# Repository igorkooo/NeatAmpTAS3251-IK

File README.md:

# NeatAmpTAS3251 — 2×170W Class D Amplifier with I2S Input & DSP

> ⚠️ **Hobby project** — no deadlines, no warranties, no guarantees. Use at your own risk.

2×170 W Class-D amplifier based on the Texas Instruments TAS3251, featuring an ESP32-S3 controller, DSP-ready architecture, USB-C programming, and a low-noise multi-rail power supply.

---

## Overview

This project builds on the excellent [NeatAmpTAS3251](https://github.com/jmf13/NeatAmpTAS3251/tree/master)
design by jmf13 and extends it with:

- **ESP32-S3** — WiFi control, I2C management of TAS3251 (volume, EQ, fault monitoring)
- **Output inductors** — dual footprint for Coilcraft XGL1712-103MED and Würth 7443631000
  for comparative distortion testing
- **ADAU1466 DSP ready** — I2S input connector, power supply, and I2C interface prepared
  for future DSP integration
- **Revised power supply** — fully redesigned for lower noise and better thermal performance
- **EasyEDA Pro** — migrated from KiCad v9 for simplified JLCPCB prototyping workflow

The complete V1.2 hardware schematic is available in [Schematic.pdf](Schematic.pdf).

<p align="center"><em>V1.2 PCB, top view</em></p>

---

## Release Notes

### Version 1.2 (schematic + PCB layout done, DRC clean, not yet produced)
- **Important fix — ESP32-S3 module pins 28/29/30 (IO35/IO36/IO37) no longer
  used.** On the ESP32-S3-WROOM-1U-N8R8 these pins are wired internally to the
  Octal PSRAM and must stay unconnected. V1.0/V1.1 used them for SW2 + C51
  (IO35) and for the SK9822 status LED data/clock (IO36/IO37 via R18/R17).
  Using them corrupts PSRAM and crashes the firmware. Changes (netlist
  [Netlist_Class_D_amp_2026-10-30.enet](Netlist_Class_D_amp_2026-10-30.enet)):
  - Module pins 28, 29, 30 → **no connection**.
  - Status LED U8 SDI → R18 (27 Ω) → **IO8** (module pin 12).
  - Status LED U8 CKI → R17 (27 Ω) → **IO9** (module pin 17).
  - SW2 + C51 (100 nF debounce) + TP12 → **IO10** (module pin 18), with a
    new **R51 10 kΩ** pull-up to 3.3V.
  - IO8, IO9 and IO10 are **no longer on H2**. H2 pins 7, 8 and 10 are now
    not connected.
- Firmware already follows this mapping: LEDs on IO8/IO9, PSRAM in Octal mode
  (see [ESP32-S3 module pinout](#esp32-s3-module-pinout) and the
  [firmware README](tas/README.md#reserved-pins-do-not-use)).
- PCB re-routed for the new connections. DRC passes. Board outline,
  connector positions and the heatsink area are unchanged from V1.0/V1.1.
- Silkscreen revision text updated to **V 1.2**.
- [Schematic.pdf](Schematic.pdf), the 3D render and the new top-view render
  ([Pictures/PCB_3D_TOP.png](Pictures/PCB_3D_TOP.png)) are re-exported from
  V1.2.
- V1.0/V1.1 boards can be reworked to the same firmware mapping. See the
  [V1.0/V1.1 rework checklist](tas/README.md#hardware-v10v11-rework-checklist-before-first-power-up),
  including the list of differences that remain after rework.

### Version 1.1
- **Important fix** — ESP32 USB-C connector was rotated 180° in V1.0, making the
  connector unusable when assembled. Now fixed.
- Added complete JLCPCB production specifications (see
  [Production Details](#production-details-jlcpcb)) as used for the first
  prototype batch.

### Version 1.0
- PCB routing completed for the first prototype revision.
- EasyEDA Pro project migrated to the new `.eprj2` project format.
- Development performed using **EasyEDA Pro V3.2.149** (V1.2 changes made
  with **V3.2.209**).
- Latest layout improvements include routing optimisation, power distribution refinement, grounding improvements, and thermal optimisation.

---

## Status

**Version:** 1.0/1.1 (Prototype), 1.2 (layout done, not yet produced)

⚠️ **V1.0/V1.1 boards need rework before the first power-up**: remove C51,
R17 and R18, and bodge the LEDs to IO8/IO9. V1.0 also needs UART flashing
because of the rotated USB-C connector. Follow the
[V1.0/V1.1 rework checklist](tas/README.md#hardware-v10v11-rework-checklist-before-first-power-up).

⚠️ This is the first public prototype release. The hardware has **not yet been validated in real-world operation**. It should be considered experimental until prototype testing is completed.

---

## Power Supply Architecture

The power supply is a multi-rail design optimised for low noise on sensitive analog paths
while keeping thermal dissipation manageable across all operating conditions.

### Rail Overview

| Rail | Voltage | Chip | Purpose |
|------|---------|------|---------|
| PVDD | 36V | External PSU | TAS3251 output stage (H-bridges) |
| 13.2V | Buck | LMQ66410 | Intermediate rail for GVDD chain |
| 12V GVDD | LDO | TPS7A4701 | TAS3251 gate drive (GVDD_A, GVDD_B, VDD) |
| 5V | Buck | LMQ66430 | System 5V bus, USB-C OR node |
| 3.3V digital | Buck | AP63203 | ESP32-S3, STM32, ADAU1466, TAS DAC_DVDD |
| 3.3V analog | LDO | TPS7A2033 | TAS3251 DAC_AVDD only |

### 12V GVDD Chain — LMQ66410 → TPS7A4701

The gate drive supply uses a two-stage approach: a switching regulator handles the large
36V→13.2V step efficiently, followed by a low-noise LDO for the final 13.2V→12V drop. ESP32 senses GOOD_13.2V on IO39 and once stable, it triggers 12V analog power via IO38.

```
PVDD (36V) → LMQ66410 (buck, 1.25MHz) → 13.2V → TPS7A4701 (LDO) → 12V GVDD
```

- **LMQ66410**: 36V input, 1.25MHz switching frequency (RT = 39.2kΩ), feedback
  R_FBT = 49.9kΩ / R_FBB = 4.12kΩ
- **TPS7A4701**: 1A LDO, 4µVrms noise, 82dB PSRR @ 100Hz, output set via ANY-OUT
  pin programming to 12.0V (pins 0P2V + 0P8V + 3P2V + 6P4V1 → GND)
- A ferrite bead (BLM31PG121SN1L) is placed between the 13.2V rail and TPS7A4701
  input for additional HF noise isolation

> **Why two stages?** A direct linear regulator from 36V to 12V at even 50mA load
> would dissipate ~1.2W in a small SMD package. The buck + LDO combination keeps
> total dissipation under 0.8W while achieving better noise performance than a
> single-stage buck alone.

### 5V Rail — LMQ66430

```
PVDD (36V) → LMQ66430 (buck, 1.25MHz) → 5V
```

- Feedback: R_FBT = 49.9kΩ / R_FBB = 24.9kΩ
- Feeds the 5V OR node (see USB-C section)
- Sources the 3.3V digital buck and 3.3V analog LDO

### 3.3V Digital Rail — AP63203

```
5V OR rail → AP63203 (fixed 3.3V buck) → 3.3V digital
```

- Fixed 3.3V output — no external feedback resistors
- Powers: ESP32-S3, STM32F030, ADAU1466 digital, TAS3251 DAC_DVDD
- Starts automatically on power-up (EN tied to VIN)
- Output: 2× 10µF ceramic + 1× 47µF electrolytic

### 3.3V Analog Rail — TPS7A2033

```
5V OR rail → TPS7A2033 (LDO) → 3.3VA
```

- Ultra-low noise LDO: 7µVrms, 95dB PSRR
- Feeds **only** TAS3251 DAC_AVDD — kept isolated from noisy digital loads
- Enabled by default via 100kΩ pull-up to 3.3V digital; ESP32-S3 can disable via
  ENABLE_3.3V GPIO IO40 for controlled power sequencing
- Input/output decoupling: 1µF Samsung CL10B105KB8NQNC (C5199872) on both pins

### USB-C Power OR

The board supports powering the digital section from either the main 36V supply
or a USB-C connection, enabling ESP32-S3 programming without the main supply present.

```
PVDD (36V) → LMQ66430 → 5V → Schottky D1 ─┐
                                             ├─ 5V OR rail → AP63203 → 3.3V digital
USB-C VBUS (5V) ────────→ 1N5819 D2 ────────┘
```

- When 36V is present: LMQ66430 supplies the 5V OR rail; USB-C Schottky is
  reverse-biased
- When USB-C only (programming mode): USB VBUS supplies 3.3V digital via AP63203;
  TAS3251 analog section remains unpowered
- 1MΩ discharge resistor on VBUS for clean hot-plug behaviour

---

## Microcontroller — ESP32-S3 controlling TAS3251

The ESP32-S3-WROOM-1U-N8R8 (8 MB flash, 8 MB Octal PSRAM) acts as the system controller, handling WiFi connectivity,
TAS3251 configuration, real-time monitoring, and user interface.

For the ESP32-S3 firmware workspace, including the Python environment, ESP-IDF
6.0.2 setup, build commands, and editor configuration, see the
[ESP32-S3 firmware README](tas/README.md) before continuing with the hardware
interface details below.

### Interface to TAS3251

All TAS3251 runtime control is via I2C (400kHz Fast Mode). The I2C bus is shared
with the ADAU1466 when fitted.

| Signal | ESP32-S3 GPIO | TAS3251 Pin | Notes |
|--------|--------------|-------------|-------|
| SDA | GPIO IO0 | SDA (54) | 6.8kΩ pull-up (R21) to 3.3V |
| SCL | GPIO IO45 | SCL (53) | 6.8kΩ pull-up (R22) to 3.3V |
| RESET_AMP | GPIO out IO42 | /RESET_AMP (27) | Active low; 10kΩ pull-up to 3.3V (default: not in reset) |
| DAC_MUTE | GPIO out IO1 | DAC_MUTE (45) | Active low; 10kΩ pull-down to GND (default: muted at boot) |
| /FAULT | GPIO in + IRQ IO41 | /FAULT (28) | Open-drain; 10kΩ pull-up; falling-edge interrupt |
| /CLIP_OTW | GPIO in + IRQ IO2 | /CLIP_OTW (29) | Open-drain; 10kΩ pull-up; falling-edge interrupt |

### TAS3251 I2C Address

Set by ADR pin (46):
- ADR → GND: address **0x90**
- ADR → 3.3V: address **0x92**

This pin is connected to ESP32 IO12.

### Switching Frequency Select — U13

The TAS3251 PWM switching frequency is set by a resistor from FREQ_ADJ (pin 18)
to AGND, broken out on jumper header **U13** (2x4, 2.54mm). Bridge exactly one
pin pair with a shunt; the current default is **pins 3-4 (10kΩ)**, giving the
highest switching frequency.

| U13 pins | R to AGND | Switching frequency |
|----------|-----------|----------------------|
| 3-4 | 10kΩ only | 768kHz ← highest (default) |
| 5-6 | 20kΩ only | 576kHz |
| 7-8 | 30kΩ only | 384kHz |
| 1-2 | Pulled to 3.3V | Target/slave mode (external sync via OSC_IOP/IOM) |

### What ESP32-S3 Controls via I2C

| Function | Register | Notes |
|----------|----------|-------|
| Power on/off | B0-P0-R2 | Startup/shutdown sequence |
| Volume (per channel) | B0-P0-R61/R62 | 0.5dB steps, −103dB to +24dB |
| Soft mute | B0-P0-R3 | Or via DAC_MUTE pin |
| EQ / crossover biquads | Book 0x8C pages | 15× BiQuad per channel; crossover HPF/LPF |
| Safeload (atomic update) | B0x8C-P5-R7C | Write 5 coefficients then set flag = 0x01 |
| Fault status read | B0-P0-R94/R95 | OC, UV, OTE, clock error — read after /FAULT IRQ |
| Volume ramp speed | B0-P0-R64 | Controls startup/shutdown ramp to prevent pops |

### Fault Handling

Both /FAULT and /CLIP_OTW are open-drain active-low outputs wired to ESP32-S3
interrupt-capable GPIOs. Implemented in `tas::SystemController` — see the
[ESP32-S3 firmware README](tas/README.md#status-led-u8u9) for the full
state/color breakdown:

1. /FAULT asserts → falling-edge ISR fires → read B0-P0-R94/R95 for fault
   detail, re-assert DAC_MUTE, and drop both channels to a conservative low
   volume — **implemented**
2. If OTE (over-temperature): wait for thermal recovery, then toggle
   RESET_AMP to clear the latched fault before resuming — **not yet
   implemented** (tracked as a `TODO` in `SystemController::handleFault()`;
   the amp currently just stays muted at low volume until manually reset)
3. /CLIP_OTW is non-latching — current firmware logs each occurrence only
   (no mute, no volume change); revisit if sustained clipping in practice
   turns out to warrant automatic volume reduction
4. Report fault status to Home Assistant via WiFi MQTT — **not yet
   implemented** (no WiFi/MQTT in the firmware yet)

### Visual Indicators

| LED | Colour | Condition |
|-----|--------|-----------|
| D_FAULT | Red | /FAULT asserted (hardware, no firmware needed) |
| D_CLIP | Yellow/Orange | /CLIP_OTW asserted (hardware, no firmware needed) |
| D_STATUS | 2× SK9822 (U8, U9), chained | ESP32-S3 controlled over a bit-banged 2-wire link (IO8 data / IO9 clock from V1.2 and reworked V1.0/V1.1; was IO36/IO37 on V1.0/V1.1 — not WS2812B) — see [Status LED (U8/U9)](tas/README.md#status-led-u8u9) in the firmware README for the color scheme |

Fault and clip LEDs are driven directly from the open-drain output through a 560Ω
resistor — they light up regardless of firmware state.

### ESP32-S3 Module Pinout

This table covers every pin of U6 (ESP32-S3-WROOM-1U-N8R8). The V1.0/V1.1
column comes from `Netlist_Class_D_amp_2026-07-23.enet`. The V1.2 column
comes from `Netlist_Class_D_amp_2026-10-30.enet`. **Bold** marks a change.

| Module pin | IO | V1.0/V1.1 connection | V1.2 | Firmware use (`tas_pins.h`) | Notes |
|-----------:|----|----------------------|-----------------|------------------------------|-------|
| 1, 40, 41 | GND | GND | GND | — | |
| 2 | 3V3 | 3.3V | 3.3V | — | |
| 3 | EN | SW1 (reset), C48, TP9 | unchanged | — | Reset button |
| 4–7 | IO4–IO7 | U7 pins 3–6 (XH 6-pin, + GND/3.3V) | unchanged | — | Spare / expansion |
| 8–11 | IO15–IO18 | H1 pins 1–4 | unchanged | — | Spare / expansion |
| 12 | IO8 | H2 pin 7 | **R18 → U8 SDI** (H2 pin 7 NC) | `TAS_PIN_STATUS_LED_SDI` | V1.0/V1.1: bodge from H2 pin 7 |
| 13 | IO19 | R16 → USB D− | unchanged | — | Native USB, reserved |
| 14 | IO20 | R15 → USB D+ | unchanged | — | Native USB, reserved |
| 15 | IO3 | H2 pin 4 | unchanged | — | Strapping pin, avoid |
| 16 | IO46 | H2 pin 6 | unchanged | — | Strapping pin, avoid |
| 17 | IO9 | H2 pin 8 | **R17 → U8 CKI** (H2 pin 8 NC) | `TAS_PIN_STATUS_LED_CKI` | V1.0/V1.1: bodge from H2 pin 8 |
| 18 | IO10 | H2 pin 10 | **SW2 + C51, R51 10 kΩ pull-up, TP12** (H2 pin 10 NC) | — (button not used yet) | User button, active low |
| 19 | IO11 | H2 pin 12 | unchanged | — | Spare (I2S test patch MCLK) |
| 20 | IO12 | H2 pin 14 (`ESP_TAS_ADR`) | unchanged | `TAS_PIN_AMP_ADDRESS` | Jumper H2 13-14 |
| 21 | IO13 | H2 pin 16 | unchanged | — | Spare (I2S test patch BCLK) |
| 22 | IO14 | H2 pin 18 | unchanged | — | Spare (I2S test patch LRCK) |
| 23 | IO21 | H2 pin 20 | unchanged | — | Spare (I2S test patch SDIN) |
| 24 | IO47 | U10 pin 3 (`DSP_RESET`) | unchanged | `TAS_PIN_DSP_RESET` | |
| 25 | IO48 | U10 pin 6 (`DSP_SELFBOOT`) | unchanged | `TAS_PIN_DSP_SELFBOOT` | |
| 26 | IO45 | SCL (TAS3251, R20 → U10) | unchanged | `TAS_PIN_I2C_SCL` | Strapping pin; 6.8 kΩ pull-up |
| 27 | IO0 | SDA (TAS3251, R19 → U10) | unchanged | `TAS_PIN_I2C_SDA` | Strapping pin (boot); 6.8 kΩ pull-up |
| **28** | **IO35** | ⚠️ SW2 + C51 to GND, TP12 | **not connected** | — | **Octal PSRAM, reserved** |
| **29** | **IO36** | ⚠️ R18 → `L_SDI` | **not connected** | — | **Octal PSRAM, reserved** |
| **30** | **IO37** | ⚠️ R17 → `L_CKI` | **not connected** | — | **Octal PSRAM, reserved** |
| 31 | IO38 | U15 pin 7 (`ENABLE_12V`) | unchanged | `TAS_PIN_ENABLE_12V` | Jumper U15 7-8 |
| 32 | IO39 | U15 pin 5 (`GOOD_13.2V`) | unchanged | `TAS_PIN_GOOD_13V2` | Jumper U15 5-6 |
| 33 | IO40 | U15 pin 3 (`ENABLE_3.3V`) | unchanged | `TAS_PIN_ENABLE_3V3_ANALOG` | Jumper U15 3-4 |
| 34 | IO41 | U14 pin 7 (`/FAULT`) | unchanged | `TAS_PIN_AMP_FAULT` | Jumper U14 7-8 |
| 35 | IO42 | U14 pin 5 (`RESET_AMP`) | unchanged | `TAS_PIN_AMP_RESET` | Jumper U14 5-6 |
| 36 | RXD0 (IO44) | H2 pin 5, TP11 | unchanged | — | UART0 console / flashing |
| 37 | TXD0 (IO43) | H2 pin 3, TP10 | unchanged | — | UART0 console / flashing |
| 38 | IO2 | U14 pin 3 (`/CLIP_OTW`) | unchanged | `TAS_PIN_AMP_CLIP_OTW` | Jumper U14 3-4 |
| 39 | IO1 | U14 pin 1 (`DAC_MUTE`) | unchanged | `TAS_PIN_DAC_MUTE` | Jumper U14 1-2 |

### ESP32-S3 Software Configuration

These settings must match the N8R8 module. They are seeded from
[`tas/sdkconfig.defaults`](tas/sdkconfig.defaults). See the
[firmware README](tas/README.md#key-sw-configuration-sdkconfigdefaults) for
details and for how to update an existing `sdkconfig`.

| Setting | Value | Reason |
|---------|-------|--------|
| Flash size | 8 MB (`CONFIG_ESPTOOLPY_FLASHSIZE_8MB`) | N8 = 8 MB Quad flash |
| PSRAM | enabled, **Octal** (`CONFIG_SPIRAM_MODE_OCT`), 80 MHz | R8 = 8 MB Octal PSRAM. Quad mode fails init. Octal mode is why IO35–IO37 are reserved |
| Pin map | [`tas/main/tas_pins.h`](tas/main/tas_pins.h) | Single source of truth. The build fails if a pin is set to IO35–IO37 |

### Startup Sequence

```
Power applied
  → AP63203 starts → 3.3V digital available
  → ESP32-S3 boots (~150ms)
  → ESP32 initialises I2C
  → ESP32 asserts ENABLE_12V → TPS7A4701 enables → 12V GVDD available
  → TAS3251 comes out of reset (RESET_AMP released)
  → ESP32 writes TAS3251 configuration via I2C (volume, EQ, crossover)
  → ESP32 drives DAC_MUTE high → audio path unmuted
  → System ready
```

---

## I2S Audio Input

The board accepts I2S audio from either:

- **LHY Audio DIR9001 module** (SPDIF → I2S, 24-bit 96kHz) via 6-pin 2.54mm connector
- **ADAU1466 DSP board** (future) via the same I2S connector
- **ESP32-S3 directly** (for testing/streaming) via the same GPIO pins

I2S connector pinout (2.54mm, 6-pin vertical):

| Pin | Signal |
|-----|--------|
| 1 | DATA (SDIN) |
| 2 | BCLK |
| 3 | LRCK |
| 4 | MCLK |
| 5 | +5V |
| 6 | GND |

27Ω series resistors are placed on all four signal lines between the connector and
TAS3251/ESP32-S3 for signal integrity and EMI reduction.

---

## Known Issues from Original Design

> As noted by the original author:
> - Silkscreen polarity for **C25, C26, C27, C28** was inverted — caps replaced with
>   non-polarised X7R ceramics in this revision, resolving the issue entirely.
> - Heatsink footprint required rework — addressed in PCB revision.

---

## Production Details (JLCPCB)

The first prototype batch (5 boards, V1.0/V1.1) was manufactured and assembled by
JLCPCB with the settings below. These are provided as a validated reference for
anyone reproducing the board.

### PCB Fabrication

| Parameter | Value |
|-----------|-------|
| Layers | 4 |
| Base Material | FR-4, TG155 |
| Dimensions | 155.45 × 134.33 mm |
| PCB Thickness | 1.6 mm |
| PCB Color / Silkscreen | Blue / White |
| Outer Copper Weight | 2 oz |
| Inner Copper Weight | 1 oz |
| Surface Finish | ENIG, Gold Thickness 1U" |
| Via Covering | Plugged |
| Min Via Hole/Diameter | 0.3 mm / (0.4/0.45 mm) |
| Electrical Test | Flying Probe Fully Test |
| Mark on PCB | Remove Mark |
| Appearance Quality | IPC Class 2 Standard |
| Board Outline Tolerance | ±0.2 mm (Regular) |
| Delivery Format | Single PCB |
| Silkscreen Technology | Ink-jet Printing |
| Build Time | 3 days (PCB only) |
| Weight (5 pcs) | 0.89 kg |

> **Why these choices:** TG155 handles output-stage heat better than standard
> TG135. ENIG provides flat pads which significantly improves assembly yield on
> the fine-pitch QFN packages (TAS3251 VQFN-56, LMQ66430 VQFN-14, TPS7A4701
> VQFN-20). Plugged vias are required for the via-in-pad thermal grid under the
> TAS3251 exposed pad. 2 oz outer copper carries the high-current speaker output
> and PVDD paths.

### SMT Assembly

| Parameter | Value |
|-----------|-------|
| PCBA Type | Standard |
| Assembly Side | Top Side |
| PCBA Qty | 5 |
| Edge Rails/Fiducials | Added by JLCPCB |
| Confirm Parts Placement | Yes |
| Bake Components | Yes |
| Photo Confirmation | Yes |
| Board Cleaning | Yes |
| Depanel & remove edge rails before delivery | Yes |
| Solder Paste | High temp. |
| Nitrogen Reflow Soldering | No |
| Flying Probe Test (post-assembly) | No |
| Function Test | No |
| Conformal Coating | No |
| Packaging | Antistatic bubble film |
| Panel Format | 1 × 1 |
| Build Time | 5–6 days (+4 days) |
| Product Classification | Audio Amplifiers — HS Code 851890 |
| Weight (5 assembled boards) | 2.29 kg |

> **Recommended for first runs:** *Confirm Parts Placement* and *Photo
> Confirmation* let you verify component orientation before reflow — worth it on
> any board with polarised or directional parts. *Board Cleaning* removes flux
> residue that could otherwise cause leakage currents on the high-impedance
> analog nodes (DAC_AVDD, AGND area).

### Not Assembled by JLCPCB (manual population)

The following components are excluded from the SMT order
(`Add into BOM = No` in EasyEDA) and must be hand-soldered:

- **L7–L14** — output filter inductors (Coilcraft XGL1712-103MED and
  Würth/Codaca MA5172-AE dual footprints) — order from Mouser
- **TP1–TP30** — test points (optional)

---

## Enclosure

⚠️ The supplied enclosure / 3D shell has **not passed the JLCPCB manufacturing review** and is **not recommended for fabrication** in its current state. It is included for reference only and requires redesign before production.

---

## Original Project

- Original design: [jmf13/NeatAmpTAS3251](https://github.com/jmf13/NeatAmpTAS3251/tree/master)
- License: [CC BY-SA 4.0](https://creativecommons.org/licenses/by-sa/4.0/) —
  this project inherits the same license.

---

## EasyEDA Pro Setup

**Recommended EasyEDA Pro version:** **V3.2.209** (V1.0/V1.1 were made with V3.2.149).

This repository includes a custom component library. To use it, create a symbolic
link inside your EasyEDA Pro libraries directory.

### macOS / Linux

```bash
# Navigate to your EasyEDA Pro libraries directory
cd ~/Documents/EasyEDA-Pro/libraries

# Create symlink to files from there so that app recognizes it
ln -s /path/to/git/NeatAmpTAS3251/EasyEDA-Pro/libraries/* .
```

### Windows

```cmd
:: Run Command Prompt as Administrator
cd %USERPROFILE%\EasyEDA-Pro\libraries

:: Create directory symlink
mklink /D NeatAmpTAS3251-lib C:\path\to\NeatAmpTAS3251\EasyEDA-Pro\libraries
```

After creating the symlink, restart EasyEDA Pro. The library will appear in the
**Libraries** panel under `NeatAmpTAS3251-lib`.

> **Note:** Replace `/path/to/git/NeatAmpTAS3251` (or `C:\path\to\NeatAmpTAS3251`) with the actual path where
> you cloned this repository. The EasyEDA Pro libraries directory location may vary
> by OS version — check your EasyEDA Pro installation settings if the default path
> above does not exist.

## Next versions updates to consider

- removing 3.3V power output as big connector with screws - keep it on headers only
- ensure cooling space around TAS chip to be 32x32mm or 40x40mm. Presently it is 23x27mm (unchanged in V1.2)
- (to be checked) add extra electrolytic capacitors in power line

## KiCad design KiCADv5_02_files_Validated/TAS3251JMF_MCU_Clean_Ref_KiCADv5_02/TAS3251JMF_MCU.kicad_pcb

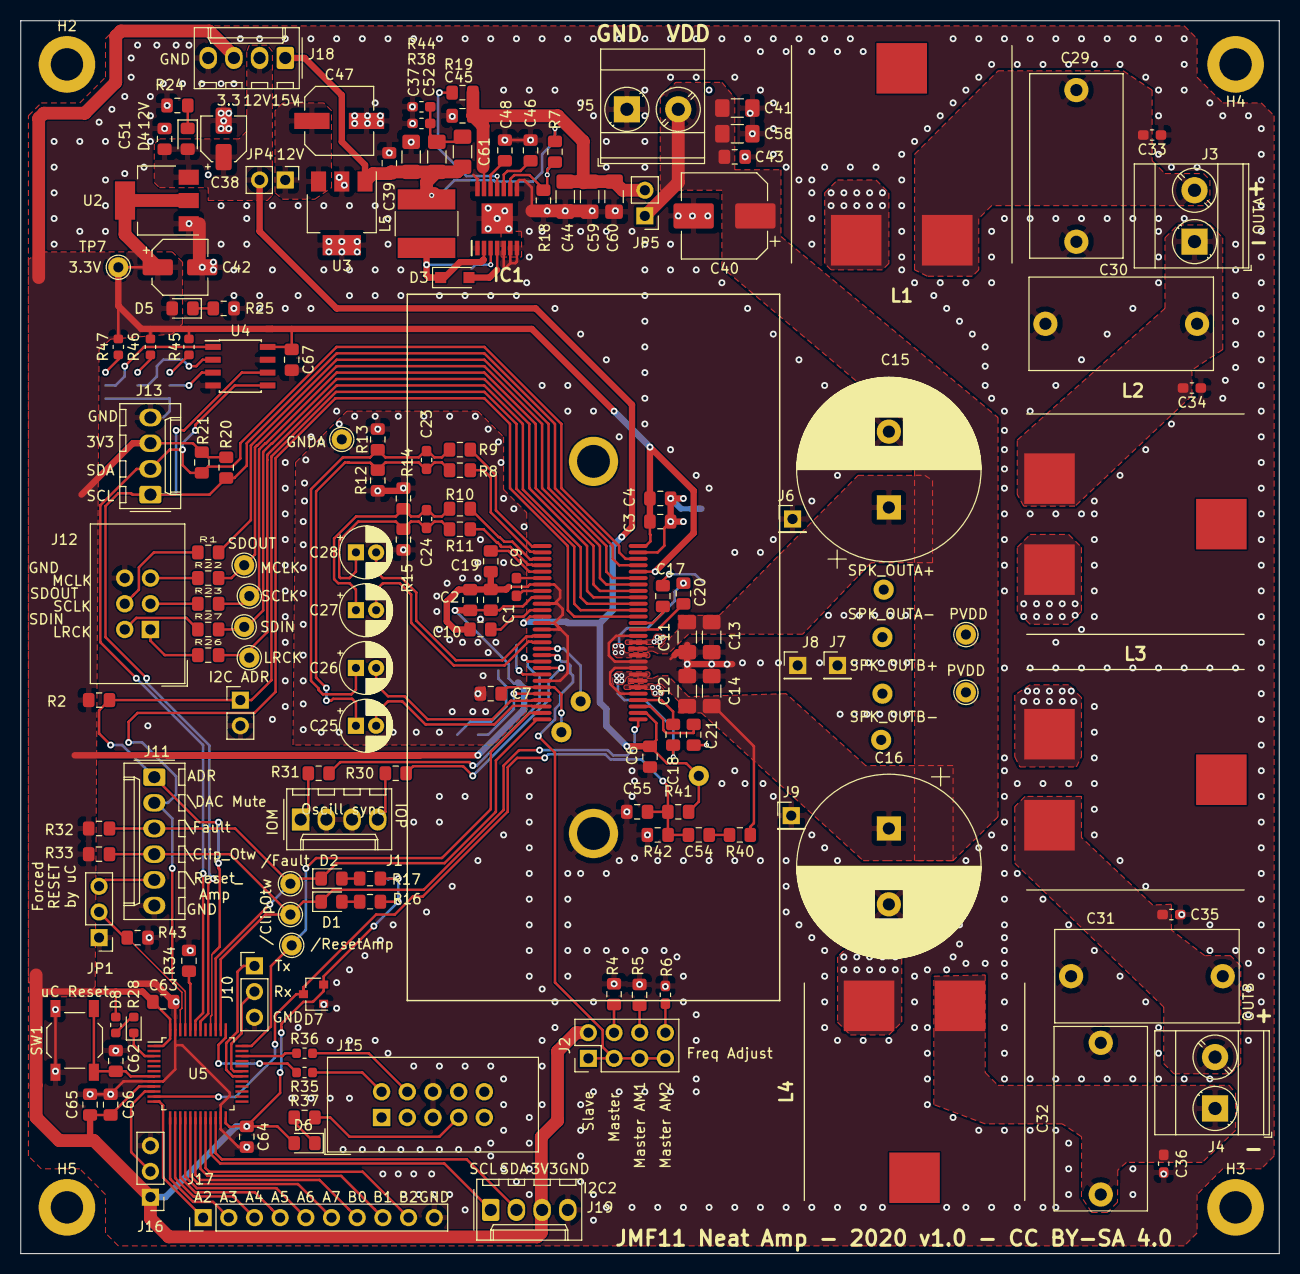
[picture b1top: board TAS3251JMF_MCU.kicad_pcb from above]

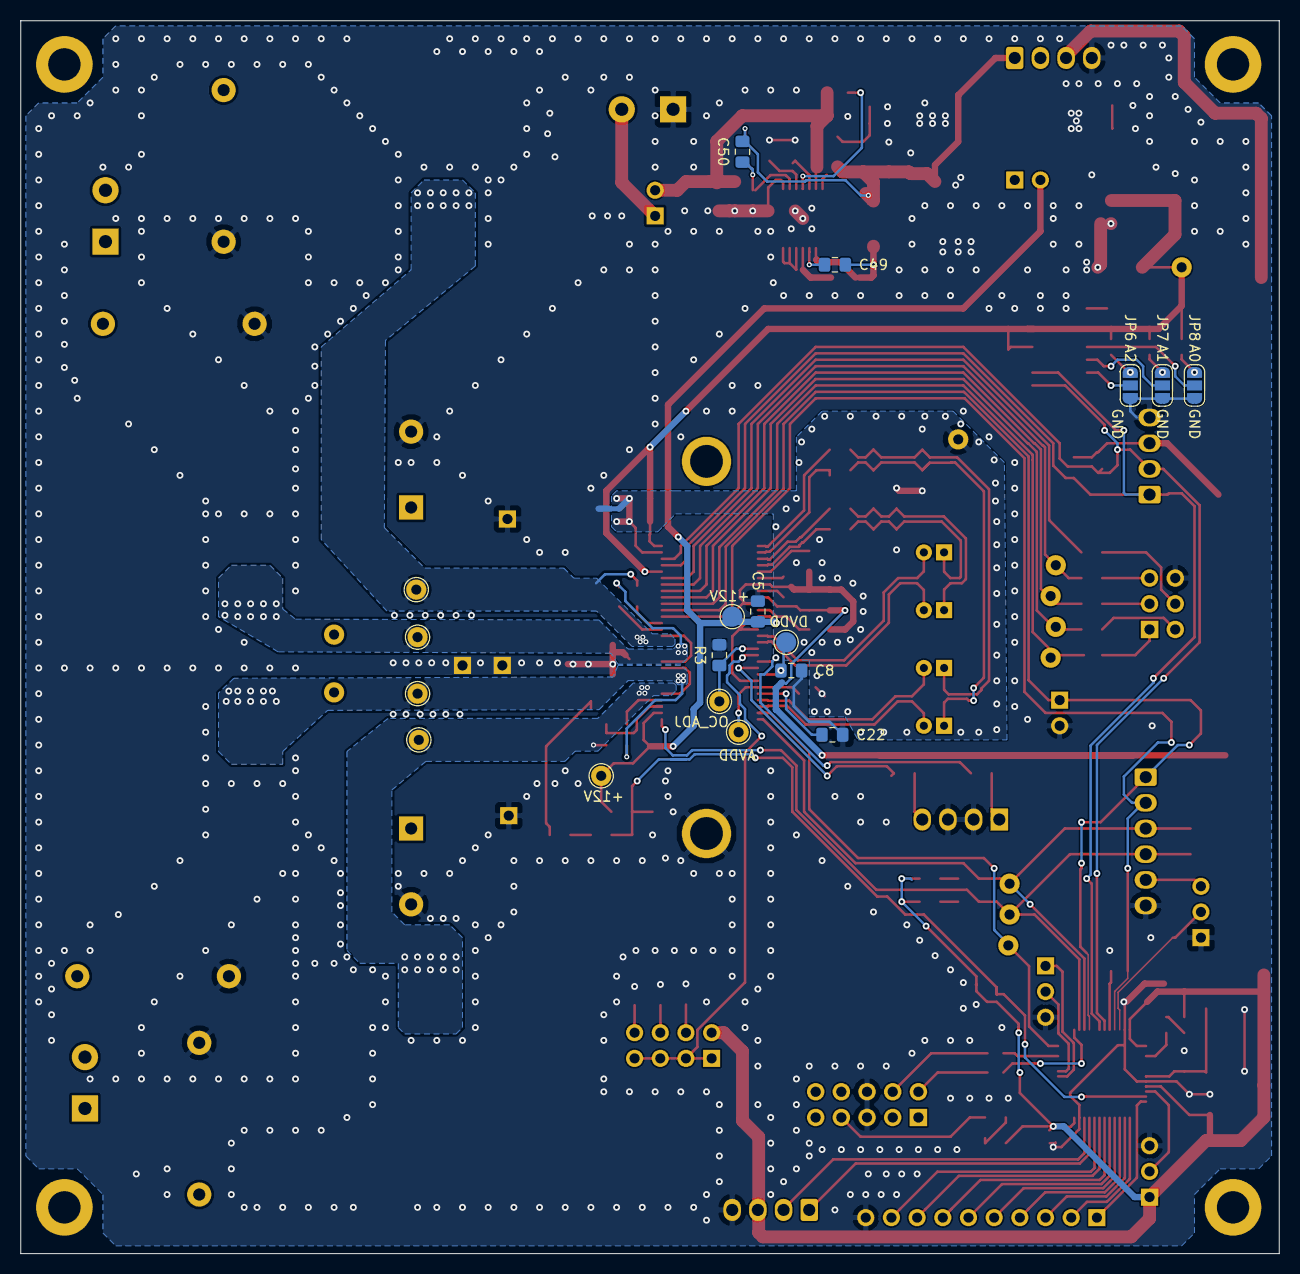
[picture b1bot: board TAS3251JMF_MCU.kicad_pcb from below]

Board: 2 copper layers, 124.5 x 121.9 mm, 180 parts (19 on the bottom side), 111 nets.

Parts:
C1, C4: 10µF; C_0805_2012Metric_Pad1.15x1.40mm_HandSolder
C2, C3, C5, C6, C10, C45, C49, C51, C62, C63, C64, C67: 0.1µF; C_0805_2012Metric_Pad1.15x1.40mm_HandSolder
C7, C8, C19, C54, C55, C66: 1µF; C_0805_2012Metric_Pad1.15x1.40mm_HandSolder
C9: 2.2µF; C_0603_1608Metric_Pad1.05x0.95mm_HandSolder
C11, C12, C13, C14, C41, C44, C58, C59, C60: 2.2µF; C_1206_3216Metric_Pad1.42x1.75mm_HandSolder
C15, C16: 2400µF; CP_Radial_D18.0mm_P7.50mm
C17, C18, C20, C21: 0.033µF; C_0805_2012Metric_Pad1.15x1.40mm_HandSolder
C22: 0.047µF; C_0805_2012Metric_Pad1.15x1.40mm_HandSolder
C23, C24, C33, C34, C35, C36: 1000pF; C_0603_1608Metric_Pad1.05x0.95mm_HandSolder
C25, C26, C27, C28: 10µF; CP_Radial_D5.0mm_P2.00mm
C29, C30, C31, C32: 0.68µF; C_Rect_L18.0mm_W9.0mm_P15.00mm_FKS3_FKP3
C37, C52, C61: 4.7µF; C_1206_3216Metric_Pad1.42x1.75mm_HandSolder
C38: 10µF; CP_Elec_4x5.8
C39, C48: 0.47µF; C_0805_2012Metric_Pad1.15x1.40mm_HandSolder
C40: 47µF; CP_Elec_8x6.2
C42: 100µF; CP_Elec_5x5.8
C43, C65: 0.01µF; C_0805_2012Metric_Pad1.15x1.40mm_HandSolder
C46, C50: 4700pF; C_0805_2012Metric_Pad1.15x1.40mm_HandSolder
C47: 47µF; CP_Elec_6.3x5.8
D1: Orange; LED_0805_2012Metric_Pad1.15x1.40mm_HandSolder
D2: Red; LED_0805_2012Metric_Pad1.15x1.40mm_HandSolder
D3: D_Schottky; D_SOD-123F
D4, D5, D6: Green; LED_0805_2012Metric_Pad1.15x1.40mm_HandSolder
D7: D_Schottky_x2_Serial_AKC; SOT-23
D8: Green; LED_0603_1608Metric
H2, H3, H4, H5: MountingHole; MountingHole_3.2mm_M3_DIN965_Pad
HS1: Heatsink; Advanced_ATS078036036-TI1OP-1099-C1-R1
IC1: LM5010MHX; SOP65P640X110-15N
J1: Oscill sync; Molex_KK-254_AE-6410-04A_1x04_P2.54mm_Vertical
J2: Freq Adjust; PinHeader_2x04_P2.54mm_Vertical
J3: OUTA; TerminalBlock_Phoenix_MKDS-3-2-5.08_1x02_P5.08mm_Horizontal
J4: OUTB; TerminalBlock_Phoenix_MKDS-3-2-5.08_1x02_P5.08mm_Horizontal
J5: PVDD; TerminalBlock_Phoenix_MKDS-3-2-5.08_1x02_P5.08mm_Horizontal
J6, J7, J8, J9: Conn_01x01_Male; PinHeader_1x01_P2.54mm_Vertical
J10, J16: Conn_01x03; PinHeader_1x03_P2.54mm_Vertical
J11: Conn_01x06; Molex_KK-254_AE-6410-06A_1x06_P2.54mm_Vertical
J12: Conn_02x03_Odd_Even; IDC-Header_2x03_P2.54mm_Vertical
J13, J18, J19: Conn_01x04; Molex_KK-254_AE-6410-04A_1x04_P2.54mm_Vertical
J15: Conn_02x05; IDC-Header_2x05_P2.54mm_Vertical
J17: Conn_01x10; PinHeader_1x10_P2.54mm_Vertical
JP1: AMP RESET Jumper; PinHeader_1x03_P2.54mm_Vertical
JP2, JP4, JP5: Jumper_2_Bridged; PinHeader_1x02_P2.54mm_Vertical
JP6, JP7, JP8: SolderJumper_3_Open; SolderJumper-3_P1.3mm_Open_RoundedPad1.0x1.5mm_NumberLabels
L1, L2, L3, L4: 10 µH; WE-HCF_201322
L5: 150µH; L_Wuerth_74404064151_Handsolder
NT1: Net-Tie_2; NetTie-2_SMD_Pad0.5mm
R1, R22, R23, R26, R27, R30, R31: 22; R_0805_2012Metric_Pad1.15x1.40mm_HandSolder
R2, R4, R32, R33, R34: 10.0k; R_0805_2012Metric_Pad1.15x1.40mm_HandSolder
R3: 22.0k; R_0805_2012Metric_Pad1.15x1.40mm_HandSolder
R5, R43: 20.0k; R_0805_2012Metric_Pad1.15x1.40mm_HandSolder
R6: 30.0k; R_0603_1608Metric_Pad1.05x0.95mm_HandSolder
R7: 5.1k; R_0805_2012Metric_Pad1.15x1.40mm_HandSolder
R8, R9, R10, R11, R25: 499; R_0805_2012Metric_Pad1.15x1.40mm_HandSolder
R12, R13, R14, R15, R40: 100k; R_0805_2012Metric_Pad1.15x1.40mm_HandSolder
R16, R17, R37: 560; R_0805_2012Metric_Pad1.15x1.40mm_HandSolder
R18: 1.02k; R_0805_2012Metric_Pad1.15x1.40mm_HandSolder
R19: 365k; R_0805_2012Metric_Pad1.15x1.40mm_HandSolder
R20, R21: 6.8k; R_0805_2012Metric_Pad1.15x1.40mm_HandSolder
R24: 1.50k; R_0805_2012Metric_Pad1.15x1.40mm_HandSolder
R28: 560; R_0603_1608Metric
R35, R36: 22; R_0603_1608Metric
R38: 0; R_0603_1608Metric_Pad1.05x0.95mm_HandSolder
R41: 12k; R_0805_2012Metric_Pad1.15x1.40mm_HandSolder
R42: 3.3k; R_0805_2012Metric_Pad1.15x1.40mm_HandSolder
R44: NoPOP; R_0603_1608Metric_Pad1.05x0.95mm_HandSolder
R45, R46, R47: 10.0k; R_0603_1608Metric
SW1: SW_Push; SW_SPST_TL3342
TP1: GND; TestPoint_THTPad_D2.0mm_Drill1.0mm
TP2: MCLK; TestPoint_THTPad_D2.0mm_Drill1.0mm
TP3: BCLK; TestPoint_THTPad_D2.0mm_Drill1.0mm
TP4: LRCK; TestPoint_THTPad_D2.0mm_Drill1.0mm
TP5: SDIN; TestPoint_THTPad_D2.0mm_Drill1.0mm
TP6: TP - Reset_Amp; TestPoint_THTPad_D2.0mm_Drill1.0mm
TP7: DAC-AVDD; TestPoint_THTPad_D2.0mm_Drill1.0mm
TP9: OC-ADJ; TestPoint_THTPad_D2.0mm_Drill1.0mm
TP10: GVDD_A; TestPoint_THTPad_D2.0mm_Drill1.0mm
TP11: GVDD_B; TestPoint_Pad_D2.0mm
TP12: AVDD; TestPoint_THTPad_D2.0mm_Drill1.0mm
TP13: DVDD; TestPoint_Pad_D2.0mm
TP14: PVDD_B; TestPoint_THTPad_D2.0mm_Drill1.0mm
TP15: PVDD_A; TestPoint_THTPad_D2.0mm_Drill1.0mm
TP16: OUTA+; TestPoint_THTPad_D2.0mm_Drill1.0mm
TP17: OUTA-; TestPoint_THTPad_D2.0mm_Drill1.0mm
TP18: OUTB+; TestPoint_THTPad_D2.0mm_Drill1.0mm
TP19: OUTB-; TestPoint_THTPad_D2.0mm_Drill1.0mm
TP20: CLIP_OTW; TestPoint_THTPad_D2.0mm_Drill1.0mm
TP21: FAULT; TestPoint_THTPad_D2.0mm_Drill1.0mm
U1: TAS3251; DKQ0056A
U2: AMS1117-3.3; SOT-223-3_TabPin2
U3: LM2940-12; SOT-223
U4: AT24C256C; SOIC-8_3.9x4.9mm_P1.27mm
U5: STM32F030C8Tx; LQFP-48_7x7mm_P0.5mm

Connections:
+3V3: C1.1, C2.1, C3.1, C4.1, C42.1, C63.1, C64.1, C65.1, C66.1, C67.1, D5.2, D6.2, D7.2, J2.2, J13.3, J16.1, J18.3, J19.3, R2.1, R16.2, R17.2, R20.2, R21.2, R28.1, R32.1, R33.1, R45.1, R46.1, R47.1, TP7.1, U1.9, U1.52, U1.56, U2.2, U4.8, U5.1, U5.9, U5.24, U5.48
+12V: C5.1, C6.1, C38.1, C51.2, D4.2, J18.2, JP4.2, R41.1, TP10.1, TP11.1, U1.12, U1.30, U2.3
+15V: C37.1, C39.1, C50.1, C52.1, C61.1, J18.1, L5.2, R7.1, U3.1
/TAS3251/ADR: J11.1, JP2.1, R2.2, U1.46, U5.40
/TAS3251/AVDD: C7.2, TP12.1, U1.23
/TAS3251/C_START: C22.1, U1.24
/TAS3251/DAC_OUTA+: R10.1, U1.3
/TAS3251/DAC_OUTA-: R11.1, U1.4
/TAS3251/DAC_OUTB+: R9.1, U1.1
/TAS3251/DAC_OUTB-: R8.1, U1.2
/TAS3251/DVDD: C8.2, TP13.1, U1.21
/TAS3251/FREQ_ADJ: J2.1, J2.3, J2.5, J2.7, U1.18
/TAS3251/GPIO_1: J17.1, U5.12
/TAS3251/GPIO_2: J17.2, U5.13
/TAS3251/GPIO_3: J17.3, U5.14
/TAS3251/GPIO_4: J17.4, U5.15
/TAS3251/GPIO_5: J17.5, U5.16
/TAS3251/GPIO_6: J17.6, U5.17
/TAS3251/GPIO_7: J17.7, U5.18
/TAS3251/GPIO_8: J17.8, U5.19
/TAS3251/GPIO_9: J17.9, U5.20
/TAS3251/I2C2_SCA: J19.2, U5.22
/TAS3251/I2C2_SCL: J19.1, U5.21
/TAS3251/INA+: C24.2, C28.1, R11.2, R15.2
/TAS3251/INA-: C24.1, C27.1, R10.2, R14.2
/TAS3251/INB+: C23.2, C26.1, R9.2, R13.2
/TAS3251/INB-: C23.1, C25.1, R8.2, R12.2
/TAS3251/LRCK-Conn: J12.1, R26.2
/TAS3251/MCLK: R22.1, TP2.1, U1.50
/TAS3251/MCLK-Conn: J12.5, R22.2
/TAS3251/OSC-IOM: R31.1, U1.19
/TAS3251/OSC-IOP: R30.1, U1.20
/TAS3251/OUTA+: C29.1, C33.2, J3.2, L1.2
/TAS3251/OUTA-: C30.1, C34.2, J3.1, L2.1
/TAS3251/OUTB+: C31.1, C35.2, J4.2, L3.2
/TAS3251/OUTB-: C32.1, C36.2, J4.1, L4.1
/TAS3251/SCL: J13.1, R20.1, U1.53, U4.6, U5.42
/TAS3251/SCLK: R23.1, TP3.1, U1.49
/TAS3251/SCLK-Conn: J12.3, R23.2
/TAS3251/SDA: J13.2, R21.1, U1.54, U4.5, U5.43
/TAS3251/SDIN: R27.1, TP5.1, U1.48
/TAS3251/SDIN-Conn: J12.2, R27.2
/TAS3251/SDOUT-Conn: J12.4, R1.1
/TAS3251/SPK_OUTA+: C17.1, L1.1, TP16.1, U1.41
/TAS3251/SPK_OUTA-: C20.1, L2.2, TP17.1, U1.39
/TAS3251/SPK_OUTB+: C18.1, L3.1, TP18.1, U1.36
/TAS3251/SPK_OUTB-: C21.1, L4.2, TP19.1, U1.34
/TAS3251/SWCLK: R35.1, U5.37
/TAS3251/SWDIO: R36.1, U5.34
/TAS3251/USART1_RX: J10.2, U5.31
/TAS3251/USART1_TX: J10.1, U5.30
/TAS3251/Volume: J16.2, U5.10
/TAS3251/\CLIP_OTW: D1.1, J11.4, R33.2, TP20.1, U1.29, U5.38
/TAS3251/\DAC_MUTE: J11.2, U1.45, U5.45
/TAS3251/\RESET-AMP: TP6.1, U1.27, U5.36
/TAS3251/\RESET-AMP-Conn: J11.5, JP1.3
GND: C1.2, C2.2, C5.2, C6.2, C8.1, C10.2, C11.1, C12.1, C13.1, C14.1, C15.2, C16.2, C19.1, C22.2, C29.2, C30.2, C31.2, C32.2, C33.1, C34.1, C35.1, C36.1, C37.2, C38.2, C39.2, C40.2, C41.1, C42.2, C43.2, C44.2, C45.2, C46.2, C47.2, C48.1, C51.1, C55.2, C58.2, C59.2, C60.2, C62.2, C63.2, C64.2, C65.2, C66.2, C67.2, D7.1, HS1.1, IC1.1, IC1.5, IC1.6, IC1.7, IC1.8, IC1.14, IC1.15, J1.2, J1.3, J5.1, J6.1, J7.1, J8.1, J9.1, J10.3, J11.6, J12.6, J13.4, J15.5, J15.6, J16.3, J17.10, J18.4, J19.4, JP1.1, JP2.2, JP6.1, JP7.1, JP8.1, NT1.1, R3.1, R4.1, R5.1, R6.1, R18.2, R24.2, R25.2, R34.2, R38.2, R42.2, R43.2, R44.2, SW1.1, U1.7, U1.10, U1.13, U1.14, U1.22, U1.33, U1.37, U1.38, U1.42, U2.1, U3.2, U3.4, U4.4, U4.7, U5.8, U5.23, U5.47
GNDA: C3.2, C4.2, C7.1, NT1.2, R12.1, R13.1, R14.1, R15.1, TP1.1, U1.55
unnamed: C9.1, U1.6
unnamed: C9.2, U1.8
unnamed: C10.1, U1.11
unnamed: C17.2, U1.44
unnamed: C18.2, U1.32
unnamed: C19.2, U1.5
unnamed: C20.2, U1.43
unnamed: C21.2, U1.31
unnamed: C44.1, C45.1, C59.1, C60.1, IC1.13, JP5.2, R19.2
unnamed: C46.1, IC1.10
unnamed: C47.1, JP4.1, U3.3
unnamed: C48.2, IC1.12
unnamed: C49.1, D3.1, IC1.2, L5.1
unnamed: C49.2, IC1.3
unnamed: C50.2, IC1.9, R7.2, R18.1
unnamed: C52.2, C61.2, R38.1, R44.1
unnamed: C54.1, R40.2
unnamed: C54.2, C55.1, D7.3, R41.2, R42.1, U5.11
unnamed: C62.1, SW1.2, U5.7
unnamed: D1.2, R16.1
unnamed: D2.2, R17.1
unnamed: D3.2, IC1.4
unnamed: D4.1, R24.1
unnamed: D5.1, R25.1
unnamed: D6.1, R37.1
unnamed: D8.1, U5.3
unnamed: D8.2, R28.2
unnamed: IC1.11, R19.1
unnamed: J1.1, R31.2
unnamed: J1.4, R30.2
unnamed: J2.4, R4.2
unnamed: J2.6, R5.2
unnamed: J2.8, R6.2
unnamed: J15.2, R35.2
unnamed: J15.4, R36.2
unnamed: J15.7, R37.2
unnamed: JP1.2, R43.1, U5.46
unnamed: JP6.2, U4.3
unnamed: JP6.3, R45.2
unnamed: JP7.2, U4.2
unnamed: JP7.3, R46.2
unnamed: JP8.2, U4.1
unnamed: JP8.3, R47.2
unnamed: R1.2, U1.51
unnamed: R3.2, TP9.1, U1.17
unnamed: R26.1, TP4.1, U1.47
unnamed: R34.1, U5.44
SPK_INA+: C28.2, U1.15
SPK_INA-: C27.2, U1.16
SPK_INB+: C26.2, U1.25
SPK_INB-: C25.2, U1.26
VDD: C11.2, C12.2, C13.2, C14.2, C15.1, C16.1, C40.1, C41.2, C43.1, C58.1, J5.2, JP5.1, R40.1, TP14.1, TP15.1, U1.35, U1.40
\FAULT: D2.1, J11.3, R32.2, TP21.1, U1.28, U5.39

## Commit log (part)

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2026-04-07 Revise README with project details and updates
    Updated project description and added new features.
2026-04-12 Opening with version 9.0.8 and saving
2026-04-15 Adding Coilcraft XGL1712103 footprint
2026-04-15 adding simulation model and 3D shape for L
2026-04-16 Adding development placeholders. Moving uC SCH to separate sheet.
2026-04-16 Adding gitignore for kicad
2026-04-19 Separating SCHs
2026-04-19 Adding new uC module
2026-04-20 Specify DSP model as ADAU1466 in README
    minor addition
2026-04-20 adding components
2026-04-21 adding ESP32 schematic
2026-04-21 Minor changes
2026-04-21 fixing names
2026-04-21 Adding signals to control for new uC
2026-04-21 minor fix to architecture
2026-04-22 modifying power supply architecture
2026-04-22 Adding LMQ66430
2026-04-22 Adding LMR/LMQ66430
2026-04-22 adding 3d shape for LMQ
2026-04-23 adding LMQ
2026-04-23 Adding PS
2026-04-24 modified PSU
2026-04-25 Initial pages
2026-04-27 putting togather 12V Analog
2026-04-27 putting cheaper 10uH
2026-04-28 adding more PSU for 5 and 3.3V
2026-04-28 starting to add ESP32
2026-05-02 conneting uC with PSU
2026-05-03 Finishing uC, connecting TAS
2026-05-03 fixing PSUs - adding caps, increasing FB curr
2026-05-04 adding few caps to amp
2026-05-07 adding i2s conn
2026-05-07 adding new lib with 1st component - MA5172
2026-05-07 updating README
2026-05-08 adding 2nd componennt
2026-05-08 minor footprint fix
2026-05-09 adding more surrounding of TAS
2026-05-09 adding caps to TAS
2026-05-10 more connections to TAS
2026-05-11 finalizing
2026-05-11 minor component swap - ESP32
2026-05-11 some component fixes
2026-05-12 adding DSP connector
2026-05-17 adding DSP dongle board
2026-05-18 minor fixes to DSP
2026-05-18 finishing DSP dongle
2026-05-19 fixing component set and annotating project
2026-05-21 replacing componnets with available
2026-05-22 fixing safety on power inputs. LMQ fixes.
2026-05-22 shortcircuiting AGND and GND
2026-05-22 inductor tuning and minor fixes
2026-05-23 Schematic V1.0 done
2026-05-26 adding few routes
2026-05-27 more traces to PCB
2026-05-27 adding copper planes and fixing power section
2026-05-28 Final PCB V1.0 - ready for assembling
2026-05-29 increasing size of PCB due to PnP limitation
2026-05-29 fixing test points. Adding DOUT signal from TAS to ext conn
2026-05-29 fixing power-OR lines
2026-05-30 PCB fixes according to sch done
2026-05-30 adding copper regions
2026-05-30 adding stitches
2026-05-30 adding components to PCB
2026-05-31 fixing parts after reviewing SCH with datasheet. Starting component placement.
2026-06-01 more fixes and PCB work
2026-06-01 more PCB work. Output pin adjusted.
2026-06-03 serious placement work done and sch fixes
2026-06-03 more work on PCB and some fixes in SCH
2026-06-04 more of PCB
2026-06-04 more routing
2026-06-05 more connections
2026-06-18 next few
2026-06-19 rerouting SCH and more routest to PCB
2026-06-20 routing done. Now tuning and cleaning
2026-06-20 ground planes and tuning
2026-06-21 adding more GND planes
2026-06-21 adding pull-up R to unconnected pin
2026-06-22 fixing holes, optimizing COG C at exit. More ground.
2026-06-22 more beautification to PCB
2026-06-23 adding project copy made with latest EasyEDA
2026-06-24 moving a track in a copy. hopefully resolving issues with versions
2026-06-24 few traces made wider. Some PVDD impruvement
2026-06-25 some fattening of tracks
2026-06-27 BOM fixes, shape tuning. plastic box
2026-06-27 case and finalization. This commit was ORDERED.

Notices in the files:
KiCADv5_02_files_Validated/TAS3251JMF_MCU_Clean_Ref_KiCADv5_02/TAS3251JMF_MCU.kicad_pcb:
JMF11 Neat Amp - 2020 v1.0 - CC BY-SA 4.0
